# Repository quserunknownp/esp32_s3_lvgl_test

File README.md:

# EV Dashboard System

Welcome to the EV Dashboard System monorepo. This repository contains the complete hardware and software stack for a high-performance electric vehicle dashboard UI, driven by an ESP32-S3 and an Arduino-based CAN bridge.

## Repository Structure

*   📁 **[Firmware](./firmware/README.md)**: Contains all software components.
    *   💻 **[Dashboard Display](./firmware/dashboard_display/README.md)**: The main ESP32-S3 firmware built with ESP-IDF and LVGL. Renders a stable ~35fps UI (optimized for PSRAM bandwidth limits) on an 800x480 RGB LCD.
    *   🔌 **[RS485 to CAN Bridge](./firmware/rs485_can_bridge/)**: Arduino code for the intermediate node that reads BMS data via RS485 and forwards it to the CAN bus.
*   📁 **[Hardware](./hardware/README.md)**: Contains all physical design and circuit files.
    *   🛠️ **[Housing (STEP)](./hardware/housing_step/)**: 3D CAD files (.step) and 2D dimensions for the dashboard's physical enclosure and brackets.
    *   ⚡ **[PCB Design](./hardware/pcb/)**: KiCad PCB design files for the custom dashboard carrier board, including manufacturing gerbers.

Please navigate to each directory to read its specific `README.md` for detailed instructions, pinouts, and hardware notes.

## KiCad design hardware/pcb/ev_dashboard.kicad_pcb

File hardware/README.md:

# Hardware Documentation

## Overview
This document provides information about the hardware components, pin mappings, and circuit configurations that make up the EV Dashboard System.

## 1. Core Components
*   **Microcontroller (MCU)**: [ESP32-S3-DevKitC-1](https://docs.espressif.com/projects/esp-dev-kits/en/latest/esp32s3/esp32-s3-devkitc-1) (N16R8)
    *   Must be the model with 16MB Flash and 8MB Octal PSRAM.
    *   > [!WARNING]
    *   > **Form Factor Note**: Be aware that certain revisions or clones of this board equipped with a **USB Type-C port** can be **2.54mm (0.1 inch, exactly one breadboard row) wider** than the standard Micro-USB versions. Please manually measure the pin pitch and total width when designing custom PCBs or 3D printed housings.
*   **Display**: 5.0-inch RGB LCD (Resolution: 800x480, Driver IC: ILI6485)
*   **CAN Transceiver**: SN65HVD230 (3.3V) or TJA1050 (requires a 5V logic level shifter).
*   **BMS Bridge**: Arduino-based RS485 to CAN translation node.

## 2. Directory Structure

*   📁 **[`housing_step/`](./housing_step/)**: Contains 3D CAD models (.step) and 2D dimensional drawings (.pdf) for the dashboard's physical enclosure and mounting brackets.
*   📁 **[`pcb/`](./pcb/)**: Contains the KiCad project files and manufacturing production data (Gerbers, BOM, Pick and Place) for the custom dashboard carrier board.

## 3. Pin Mappings

### RGB Display Interface
*   **Control**: `PCLK` (11), `HSYNC` (12), `VSYNC` (13), `DE` (14)
*   **Red**: `R3`~`R7` (4, 5, 6, 7, 15)
*   **Green**: `G2`~`G7` (16, 17, 18, 8, 3, 9)
*   **Blue**: `B3`~`B7` (42, 41, 40, 39, 38)

### Peripherals
*   **CAN RX**: GPIO 2
*   **CAN TX**: GPIO 1
*   **Drive Mode Switch**: GPIO 10 (Uses internal pull-up, triggers Active Low when shorted to GND).

[⬅️ Back to Main Repository](../README.md)

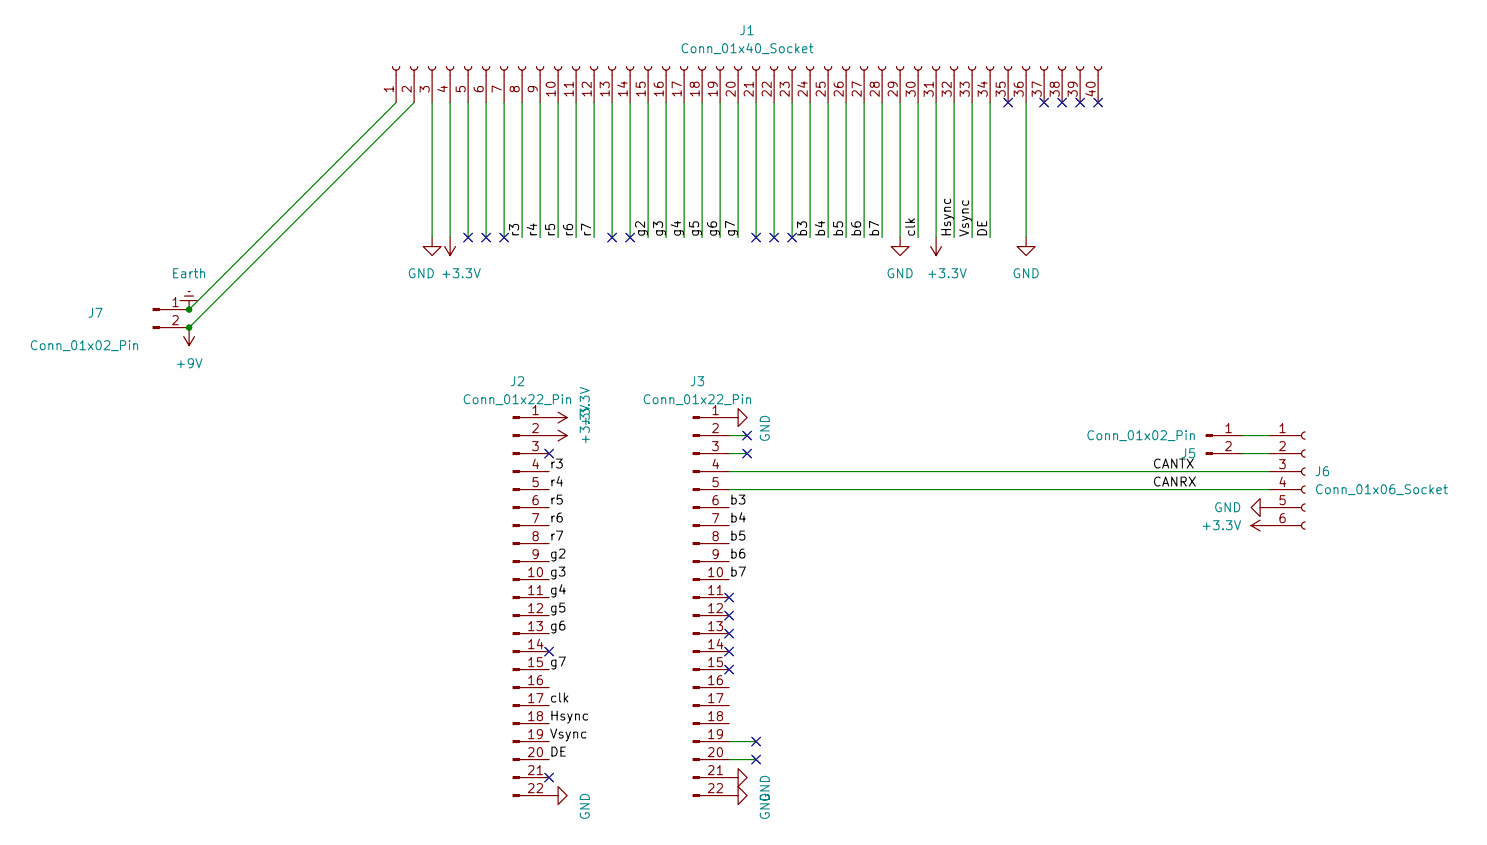
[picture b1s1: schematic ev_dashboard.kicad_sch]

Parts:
J1: Conn_01x40_Socket; FPC05
J2, J3: Conn_01x22_Pin; PinHeader_1x22_P2.54mm_Vertical
J5, J7: Conn_01x02_Pin; Samtec_HPM-02-01-x-S_Straight_1x02_Pitch5.08mm
J6: Conn_01x06_Socket; PinHeader_1x06_P2.54mm_Vertical

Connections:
+3.3V: J1.4, J1.31, J2.1, J2.2, J6.6
+9V: J1.2, J7.2
/CANRX: J3.5, J6.4
/CANTX: J3.4, J6.3
/DE: J1.34, J2.20
/Hsync: J1.32, J2.18
/Vsync: J1.33, J2.19
/b3: J1.24, J3.6
/b4: J1.25, J3.7
/b5: J1.26, J3.8
/b6: J1.27, J3.9
/b7: J1.28, J3.10
/clk: J1.30, J2.17
/g2: J1.15, J2.9
/g3: J1.16, J2.10
/g4: J1.17, J2.11
/g5: J1.18, J2.12
/g6: J1.19, J2.13
/g7: J1.20, J2.15
/r3: J1.8, J2.4
/r4: J1.9, J2.5
/r5: J1.10, J2.6
/r6: J1.11, J2.7
/r7: J1.12, J2.8
Earth: J1.1, J7.1
GND: J1.3, J1.29, J1.36, J2.22, J3.1, J3.21, J3.22, J6.5
unnamed: J5.1, J6.1
unnamed: J5.2, J6.2

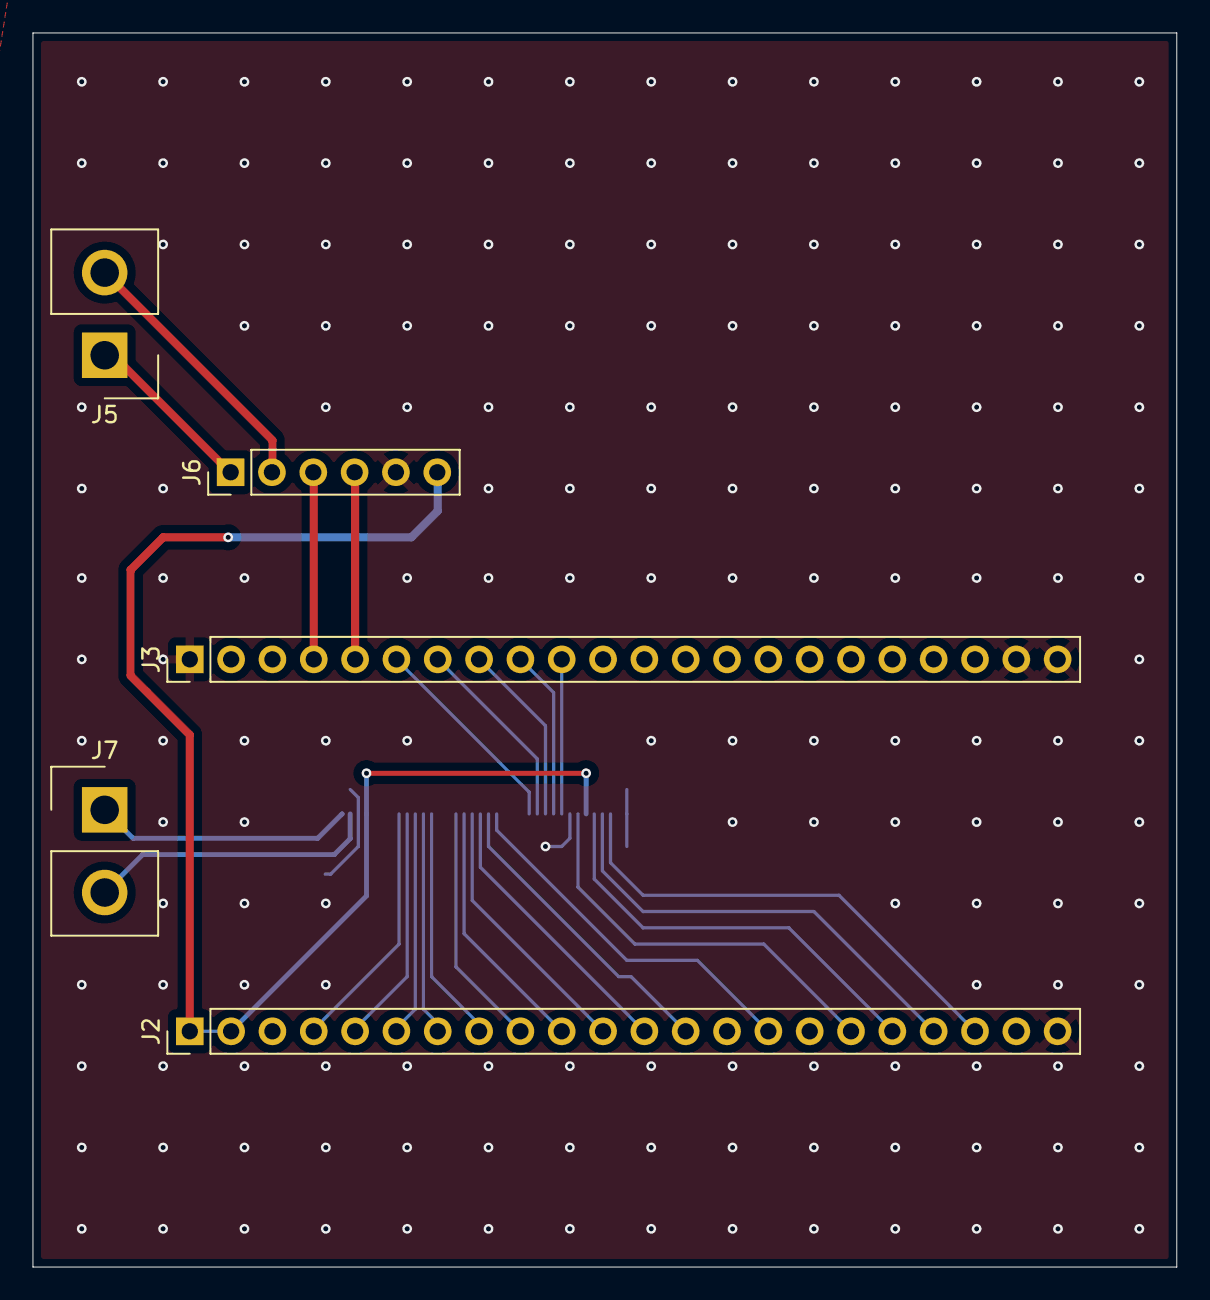
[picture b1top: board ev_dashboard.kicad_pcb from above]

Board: 2 copper layers, 70.3 x 75.8 mm, 6 parts (1 on the bottom side), 28 nets.

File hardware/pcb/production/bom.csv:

Designator,Footprint,Quantity,Value,LCSC Part #
J1,FPC05,1,FC-05D40P11H20,C23398806
"J2, J3",PinHeader_1x22_P2.54mm_Vertical,2,Conn_01x22_Pin,
"J5, J7",Samtec_HPM-02-01-x-S_Straight_1x02_Pitch5.08mm,2,Conn_01x02_Pin,
J6,PinHeader_1x06_P2.54mm_Vertical,1,Conn_01x06_Socket,

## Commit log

2026-06-11 Initial commit: ESP32-S3 N16R8 LVGL Dashboard
2026-06-11 Add README.md with project overview
2026-06-11 Update README.md to mark UI features as temporary
2026-06-11 Refine UI temporary note wording
2026-06-13 Fix LVGL rendering delay and update UI to LED indicator
2026-06-13 Update README with recent architecture, PCLK notes, and CAN UI features
2026-06-13 Refactor: Move ESP-IDF project into firmware/ directory for monorepo structure
2026-06-13 Create Housing
2026-06-13 Docs: Add software and hardware documentation files
2026-06-13 Docs: Rename software.md to firmware/firmware.md
2026-06-13 Docs: Rename folder-specific markdown files to README.md for GitHub auto-render
2026-06-13 Docs: Add ESP32-S3-DevKitC-1 link and warning about Type-C board width
2026-06-13 Housing Files Upload
2026-06-13 Docs: Move CAD and drawing files to hardware/cad directory
2026-06-13 Docs: Rename hardware/cad to hardware/housing_step
2026-06-13 Hardware: Add pcb directory
2026-06-13 Hardware: Add KiCad PCB design files and production data
2026-06-13 Docs: Add KiCad temporary files to .gitignore
2026-06-13 Refactor: Restructure firmware folders and rename CAD/PCB files
2026-06-13 Docs: Update root README.md for new monorepo structure
2026-06-13 Fix: Add missing cpp and header files for RS485 bridge
2026-06-13 Fix: Remove absolute path from main.cpp comments
2026-06-13 Docs: Restore firmware/README.md to describe sub-projects
2026-06-13 Docs: Rewrite all READMEs in English and add navigation links
2026-06-13 Docs: Correct FPS from 60fps to ~35fps reflecting PCLK limits
2026-06-13 Docs: Add JSON License (The Software shall be used for Good, not Evil)
2026-06-13 Docs: Update LICENSE copyright to credit quserp, r4m1, and GBung-E (GIST)
2026-06-13 Docs: Add JSON License title to the top of the LICENSE file
2026-06-13 Docs: Format LICENSE to meet GitHub Licensee standards for JSON License
2026-06-13 Docs: Update LICENSE to Dual License model (Beerware + Commercial)
